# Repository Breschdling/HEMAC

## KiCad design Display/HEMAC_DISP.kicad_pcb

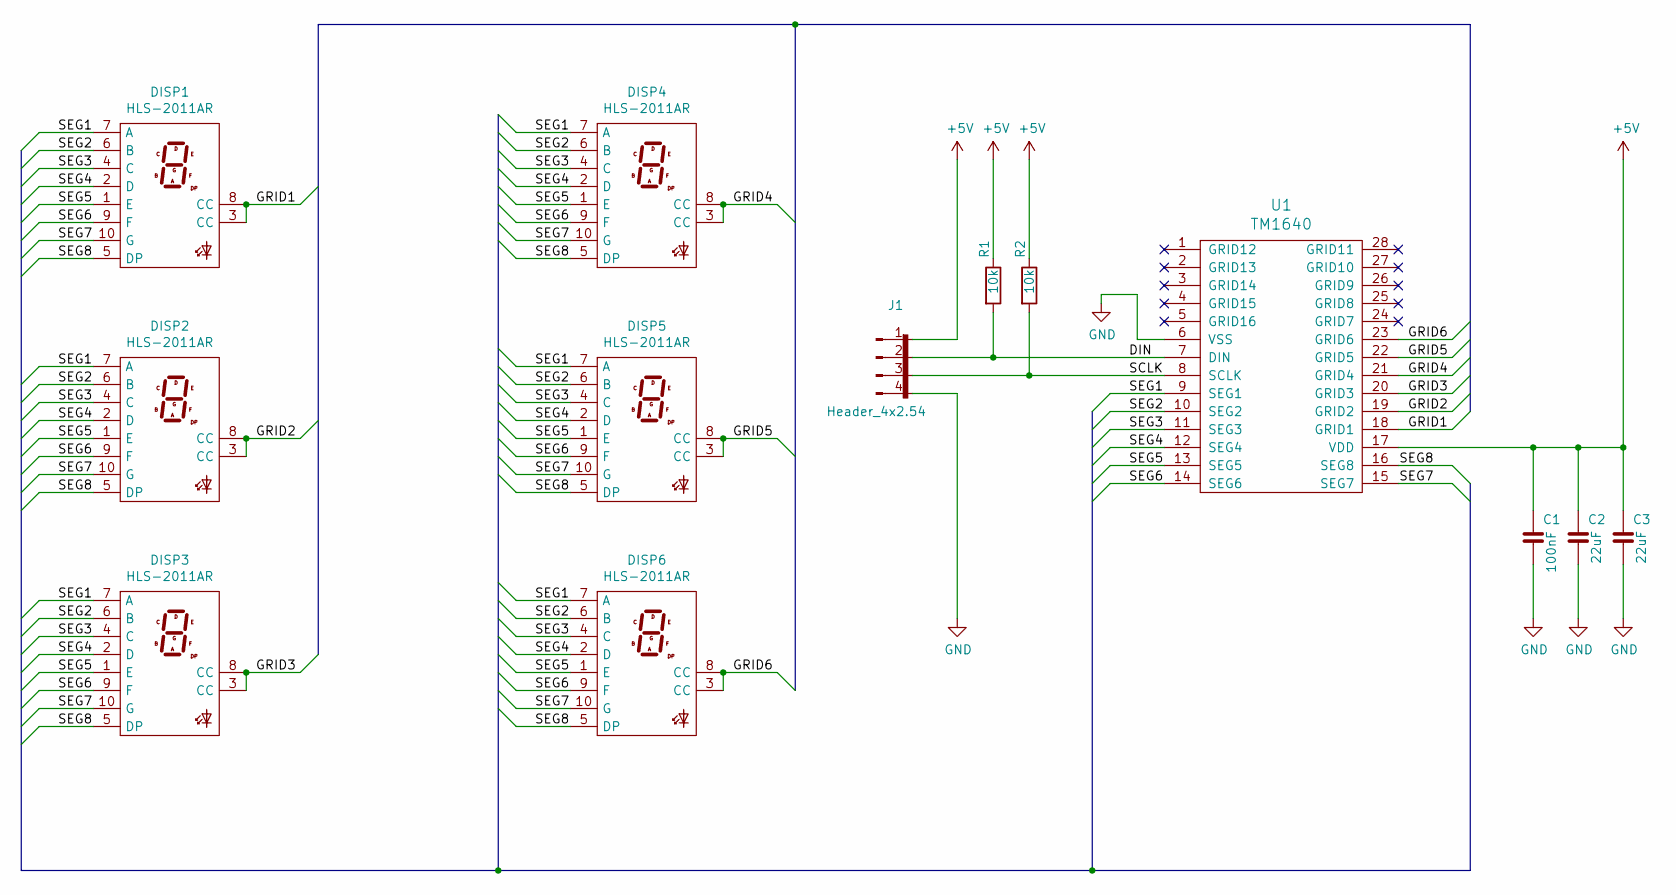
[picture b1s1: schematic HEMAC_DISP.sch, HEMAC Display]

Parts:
C1: 100nF; C_0805
C2, C3: 22uF; C_0805
DISP1, DISP2, DISP3, DISP4, DISP5, DISP6: HLS-2011AR; HLS-2011_Via
J1: Header_4x2.54; PinHeader_1x04_P2.54mm_Vertical
R1, R2: 10k; R_0805
U1: TM1640; SOIC28P127_1740X1015X255L60X40M

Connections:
+5V: C1.1, C2.1, C3.1, J1.1, R1.1, R2.1, U1.17 (VDD)
/DIN: J1.2, R1.2, U1.7 (DIN)
/GRID1: DISP1.3 (CC), DISP1.8 (CC), U1.18 (GRID1)
/GRID2: DISP2.3 (CC), DISP2.8 (CC), U1.19 (GRID2)
/GRID3: DISP3.3 (CC), DISP3.8 (CC), U1.20 (GRID3)
/GRID4: DISP4.3 (CC), DISP4.8 (CC), U1.21 (GRID4)
/GRID5: DISP5.3 (CC), DISP5.8 (CC), U1.22 (GRID5)
/GRID6: DISP6.3 (CC), DISP6.8 (CC), U1.23 (GRID6)
/SCLK: J1.3, R2.2, U1.8 (SCLK)
/SEG1: DISP1.7 (A), DISP2.7 (A), DISP3.7 (A), DISP4.7 (A), DISP5.7 (A), DISP6.7 (A), U1.9 (SEG1)
/SEG2: DISP1.6 (B), DISP2.6 (B), DISP3.6 (B), DISP4.6 (B), DISP5.6 (B), DISP6.6 (B), U1.10 (SEG2)
/SEG3: DISP1.4 (C), DISP2.4 (C), DISP3.4 (C), DISP4.4 (C), DISP5.4 (C), DISP6.4 (C), U1.11 (SEG3)
/SEG4: DISP1.2 (D), DISP2.2 (D), DISP3.2 (D), DISP4.2 (D), DISP5.2 (D), DISP6.2 (D), U1.12 (SEG4)
/SEG5: DISP1.1 (E), DISP2.1 (E), DISP3.1 (E), DISP4.1 (E), DISP5.1 (E), DISP6.1 (E), U1.13 (SEG5)
/SEG6: DISP1.9 (F), DISP2.9 (F), DISP3.9 (F), DISP4.9 (F), DISP5.9 (F), DISP6.9 (F), U1.14 (SEG6)
/SEG7: DISP1.10 (G), DISP2.10 (G), DISP3.10 (G), DISP4.10 (G), DISP5.10 (G), DISP6.10 (G), U1.15 (SEG7)
/SEG8: DISP1.5 (DP), DISP2.5 (DP), DISP3.5 (DP), DISP4.5 (DP), DISP5.5 (DP), DISP6.5 (DP), U1.16 (SEG8)
GND: C1.2, C2.2, C3.2, J1.4, U1.6 (VSS)

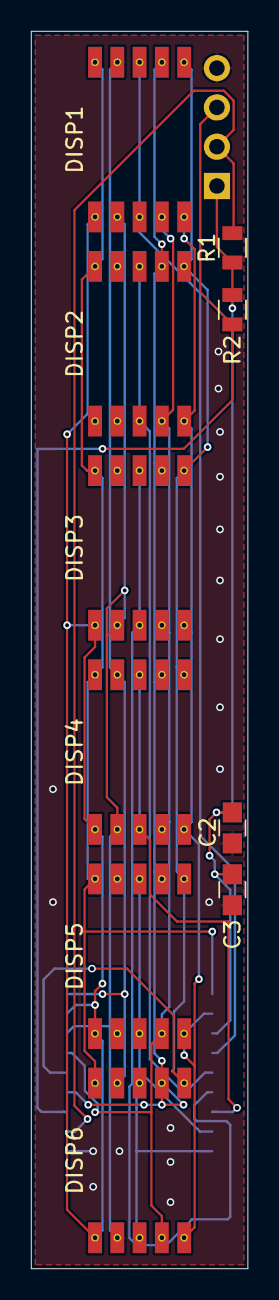
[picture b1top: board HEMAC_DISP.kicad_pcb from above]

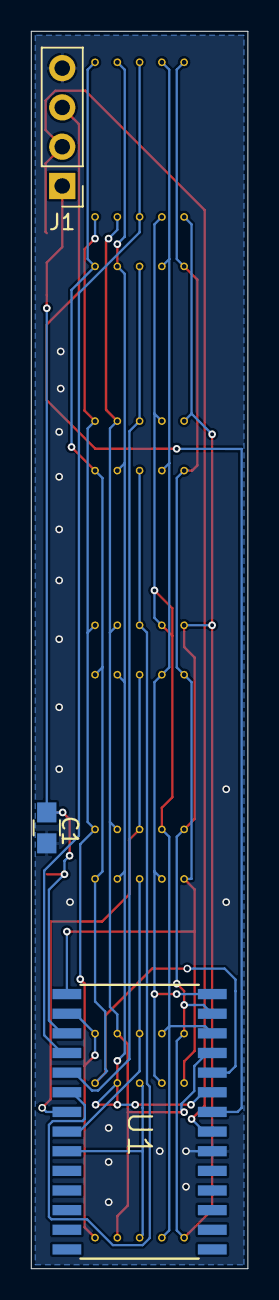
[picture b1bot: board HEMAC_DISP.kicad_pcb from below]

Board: 2 copper layers, 14.0 x 80.0 mm, 13 parts (3 on the bottom side), 18 nets.

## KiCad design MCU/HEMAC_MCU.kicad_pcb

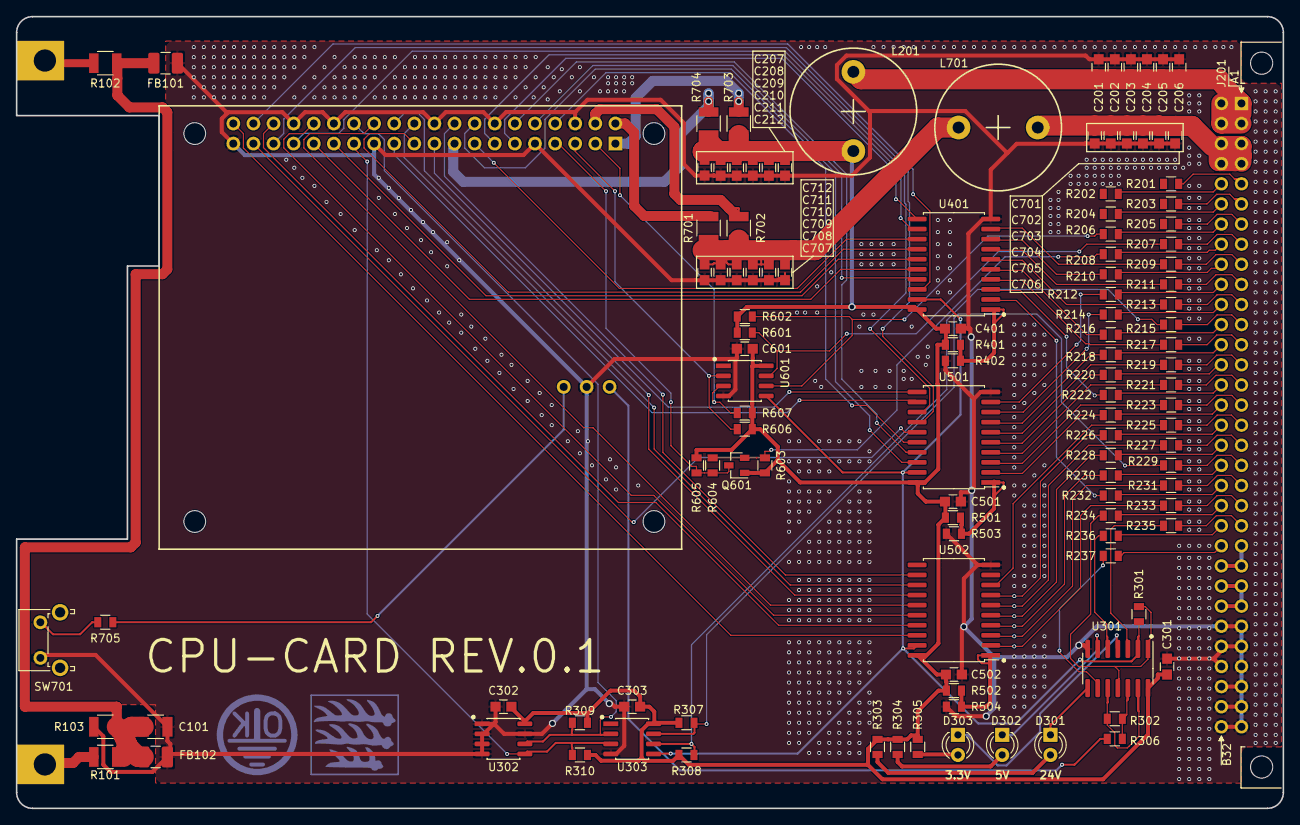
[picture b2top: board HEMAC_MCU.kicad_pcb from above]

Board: 2 copper layers, 160.0 x 100.0 mm, 119 parts (0 on the bottom side), 126 nets.

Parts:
C101: 1nF; C_1210
C201, C207, C301, C302, C303, C401, C501, C502, C601, C706, C712: 100nF; C_0805
C202, C203, C204, C205, C206, C208, C209, C210, C211, C212, C701, C702, C703, C704, C705, C707, C708, C709, C710, C711: 10uF; C_0805
D301, D302, D303: LED; LED_D3.0mm
FB101, FB102: 100R; FB_1210_3225Metric_Pad1.42x2.65mm_HandSolder
J201: DIN41612_2x32_B; DIN41612_B_2x32_Horizontal
L201, L701: 120uH_3A; 16mm_Radial
M101: Eurocard_Handle; EuroCard_Handle
Q601: 2N7002; SOT-23
R101, R102, R701, R702, R703, R704: 0R; R_1210
R103: 1M; R_1210
R201, R202, R203, R204, R205, R206, R207, R208, R209, R210, R211, R212, R213, R214, R215, R216, R217, R218, R219, R220, R221, R222, R223, R224, R225, R226, R227, R228, R229, R230, R231, R232, R233, R234, R235, R236, R237, R604, R705: 100R; R_0805
R301, R302, R306: 0R; R_0805
R303, R304, R305: 220R; R_0805
R307, R308, R309, R310: 3k9; R_0805
R401, R402, R501, R502, R503, R504: 1k; R_0805
R601, R602, R606, R607: 1k8; R_0805
R603, R605: 4k7; R_0805
SW701: Tactile_90_Degeree; SW_Tactile_SPST_Angled_PTS645Vx58-2LFS
U301: 74HC14D; SOIC-14_3.9x8.7mm_P1.27mm
U302: CAT24C32; SOIC-8_3.9x4.9mm_P1.27mm
U303, U601: PCA9515; SOIC-8_3.9x4.9mm_P1.27mm
U401, U501, U502: 74HC245; SOIC-20W_7.5x12.8mm_P1.27mm
X701: RPI_4+Run; raspberrypi4

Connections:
+3V3: C207.1, C208.1, C209.1, C210.1, C211.1, C212.1, C301.1, C302.1, C303.1, C401.1, C501.1, C502.1, C601.1, L201.2, Q601.1, R303.1, R304.1, R305.1, R307.1, R308.1, R309.1, R310.1, R401.2, R501.2, R502.2, R601.1, R602.1, R603.1, R605.1, R606.1, R607.1, R703.2, R704.2, U301.14, U302.8, U303.8, U401.20, U501.20, U502.20, U601.8
+5V: C701.1, C702.1, C703.1, C704.1, C705.1, C706.1, J201.A3, J201.A4, J201.B3, J201.B4, L701.2
+24V: J201.A23, J201.A24, J201.B24
/Bus/1_wire: Q601.2, R208.1, R603.2, R604.2
/Bus/#RESET: R234.1, R301.2, U301.1, U301.11
/Bus/CE0: R227.1, U502.6
/Bus/CE1: R228.1, U502.5
/Bus/CE2: R231.1, U502.3
/Bus/GPI5: R216.1, U401.5
/Bus/GPI6: R217.1, U401.4
/Bus/GPI17: R209.1, U401.9
/Bus/GPI22: R211.1, U401.7
/Bus/GPI27: R210.1, U401.8
/Bus/GPO23: R224.1, U501.2
/Bus/GPO24: R225.1, U502.8
/Bus/GPO25: R226.1, U502.7
/Bus/GPO26: R220.1, U501.5
/Bus/I2C_SCL: R207.1, R601.2, U601.7
/Bus/I2C_SDA: R206.1, R602.2, U601.6
/Bus/ID_SC: R229.1, R307.2, U303.7
/Bus/ID_SD: R215.1, R308.2, U303.6
/Bus/MISO: R213.1, U401.6
/Bus/MOSI: R212.1, U501.9
/Bus/PCM_CLK: R223.1, U501.3
/Bus/PCM_DIN: R232.1, U401.2
/Bus/PCM_DOUT: R233.1, U502.2
/Bus/PCM_FS: R219.1, U501.6
/Bus/PWM0: R230.1, U502.4
/Bus/PWM1: R218.1, U501.7
/Bus/PWR_3V3: R235.1, U301.3
/Bus/PWR_5V: R236.1, U301.5
/Bus/PWR_24V: R237.1, U301.9
/Bus/SCLK: R214.1, U501.8
/Bus/UART0_RXD: R222.1, U401.3
/Bus/UART0_TXD: R221.1, U501.4
/Computer/GPIO2: R607.2, U601.3, X701.3
/Computer/GPIO3: R606.2, U601.2, X701.5
/Computer/GPIO4: Q601.3, R604.1, R605.2, X701.7
/Computer/GPIO5: U401.15, X701.29
/Computer/GPIO6: U401.16, X701.31
/Computer/GPIO7: U502.15, X701.26
/Computer/GPIO8: U502.14, X701.24
/Computer/GPIO9: U401.14, X701.21
/Computer/GPIO10: U501.11, X701.19
/Computer/GPIO11: U501.12, X701.23
/Computer/GPIO12: U502.16, X701.32
/Computer/GPIO13: U501.13, X701.33
/Computer/GPIO14: U501.16, X701.8
/Computer/GPIO15: U401.17, X701.10
/Computer/GPIO16: U502.17, X701.36
/Computer/GPIO17: U401.11, X701.11
/Computer/GPIO18: U501.17, X701.12
/Computer/GPIO19: U501.14, X701.35
/Computer/GPIO20: U401.18, X701.38
/Computer/GPIO21: U502.18, X701.40
/Computer/GPIO22: U401.13, X701.15
/Computer/GPIO23: U501.18, X701.16
/Computer/GPIO24: U502.12, X701.18
/Computer/GPIO25: U502.13, X701.22
/Computer/GPIO26: U501.15, X701.37
/Computer/GPIO27: U401.12, X701.13
/Computer/ID_SC_RPI: R309.2, U302.6, U303.2, X701.28
/Computer/ID_SD_RPI: R310.2, U302.5, U303.3, X701.27
/Computer/RUN_PG2: R306.1, X701.43
/Inputs/CE: R301.1, U301.2, U303.5, U401.19, U501.19, U502.19, U601.5
Earth: C101.1, FB101.1, FB102.1, R101.1, R102.1, R103.1
GND: C101.2, C201.2, C202.2, C203.2, C204.2, C205.2, C206.2, C207.2, C208.2, C209.2, C210.2, C211.2, C212.2, C301.2, C302.2, C303.2, C401.2, C501.2, C502.2, C601.2, C701.2, C702.2, C703.2, C704.2, C705.2, C706.2, C707.2, C708.2, C709.2, C710.2, C711.2, C712.2, FB101.2, FB102.2, J201.A27, J201.A28, J201.A29, J201.A30, J201.A31, J201.A32, J201.B27, J201.B28, J201.B29, J201.B30, J201.B31, J201.B32, R103.2, R402.1, R503.1, R504.1, SW701.1, U301.7, U302.1, U302.2, U302.3, U302.4, U302.7, U303.4, U401.10, U501.10, U502.10, U601.4, X701.6, X701.9, X701.14, X701.20, X701.25, X701.30, X701.34, X701.39, X701.42
unnamed: C201.1, C202.1, C203.1, C204.1, C205.1, C206.1, J201.A1, J201.A2, J201.B1, J201.B2, L201.1
unnamed: C707.1, C708.1, C709.1, C710.1, C711.1, C712.1, L701.1, R701.2, R702.2
unnamed: D301.1, U301.8
unnamed: D301.2, R303.2
unnamed: D302.1, U301.6
unnamed: D302.2, R304.2
unnamed: D303.1, U301.4
unnamed: D303.2, R305.2
unnamed: J201.A5, R201.2
unnamed: J201.A6, R203.2
unnamed: J201.A7, R205.2
unnamed: J201.A8, R207.2
unnamed: J201.A9, R209.2
unnamed: J201.A10, R211.2
unnamed: J201.A11, R213.2
unnamed: J201.A12, R215.2
unnamed: J201.A13, R217.2
unnamed: J201.A14, R219.2
unnamed: J201.A15, R221.2
unnamed: J201.A16, R223.2
unnamed: J201.A17, R225.2
unnamed: J201.A18, R227.2
unnamed: J201.A19, R229.2
unnamed: J201.A20, R231.2
unnamed: J201.A21, R233.2
unnamed: J201.A22, R235.2
unnamed: J201.B5, R202.2
unnamed: J201.B6, R204.2
unnamed: J201.B7, R206.2
unnamed: J201.B8, R208.2
unnamed: J201.B9, R210.2
unnamed: J201.B10, R212.2
unnamed: J201.B11, R214.2
unnamed: J201.B12, R216.2
unnamed: J201.B13, R218.2
unnamed: J201.B14, R220.2
unnamed: J201.B15, R222.2
unnamed: J201.B16, R224.2
unnamed: J201.B17, R226.2
unnamed: J201.B18, R228.2
unnamed: J201.B19, R230.2
unnamed: J201.B20, R232.2
unnamed: J201.B21, R234.2
unnamed: J201.B22, R236.2
unnamed: J201.B23, R237.2
unnamed: M101.1, R101.2
unnamed: M101.2, R102.2
unnamed: R302.1, R306.2, U301.12
unnamed: R302.2, U301.10, U301.13
unnamed: R401.1, R402.2, U401.1
unnamed: R501.1, R503.2, U501.1
unnamed: R502.1, R504.2, U502.1
unnamed: R701.1, X701.2
unnamed: R702.1, X701.4
unnamed: R703.1, X701.1
unnamed: R704.1, X701.17
unnamed: R705.1, X701.41
unnamed: R705.2, SW701.2
VDC: J201.A25, J201.A26, J201.B25, J201.B26

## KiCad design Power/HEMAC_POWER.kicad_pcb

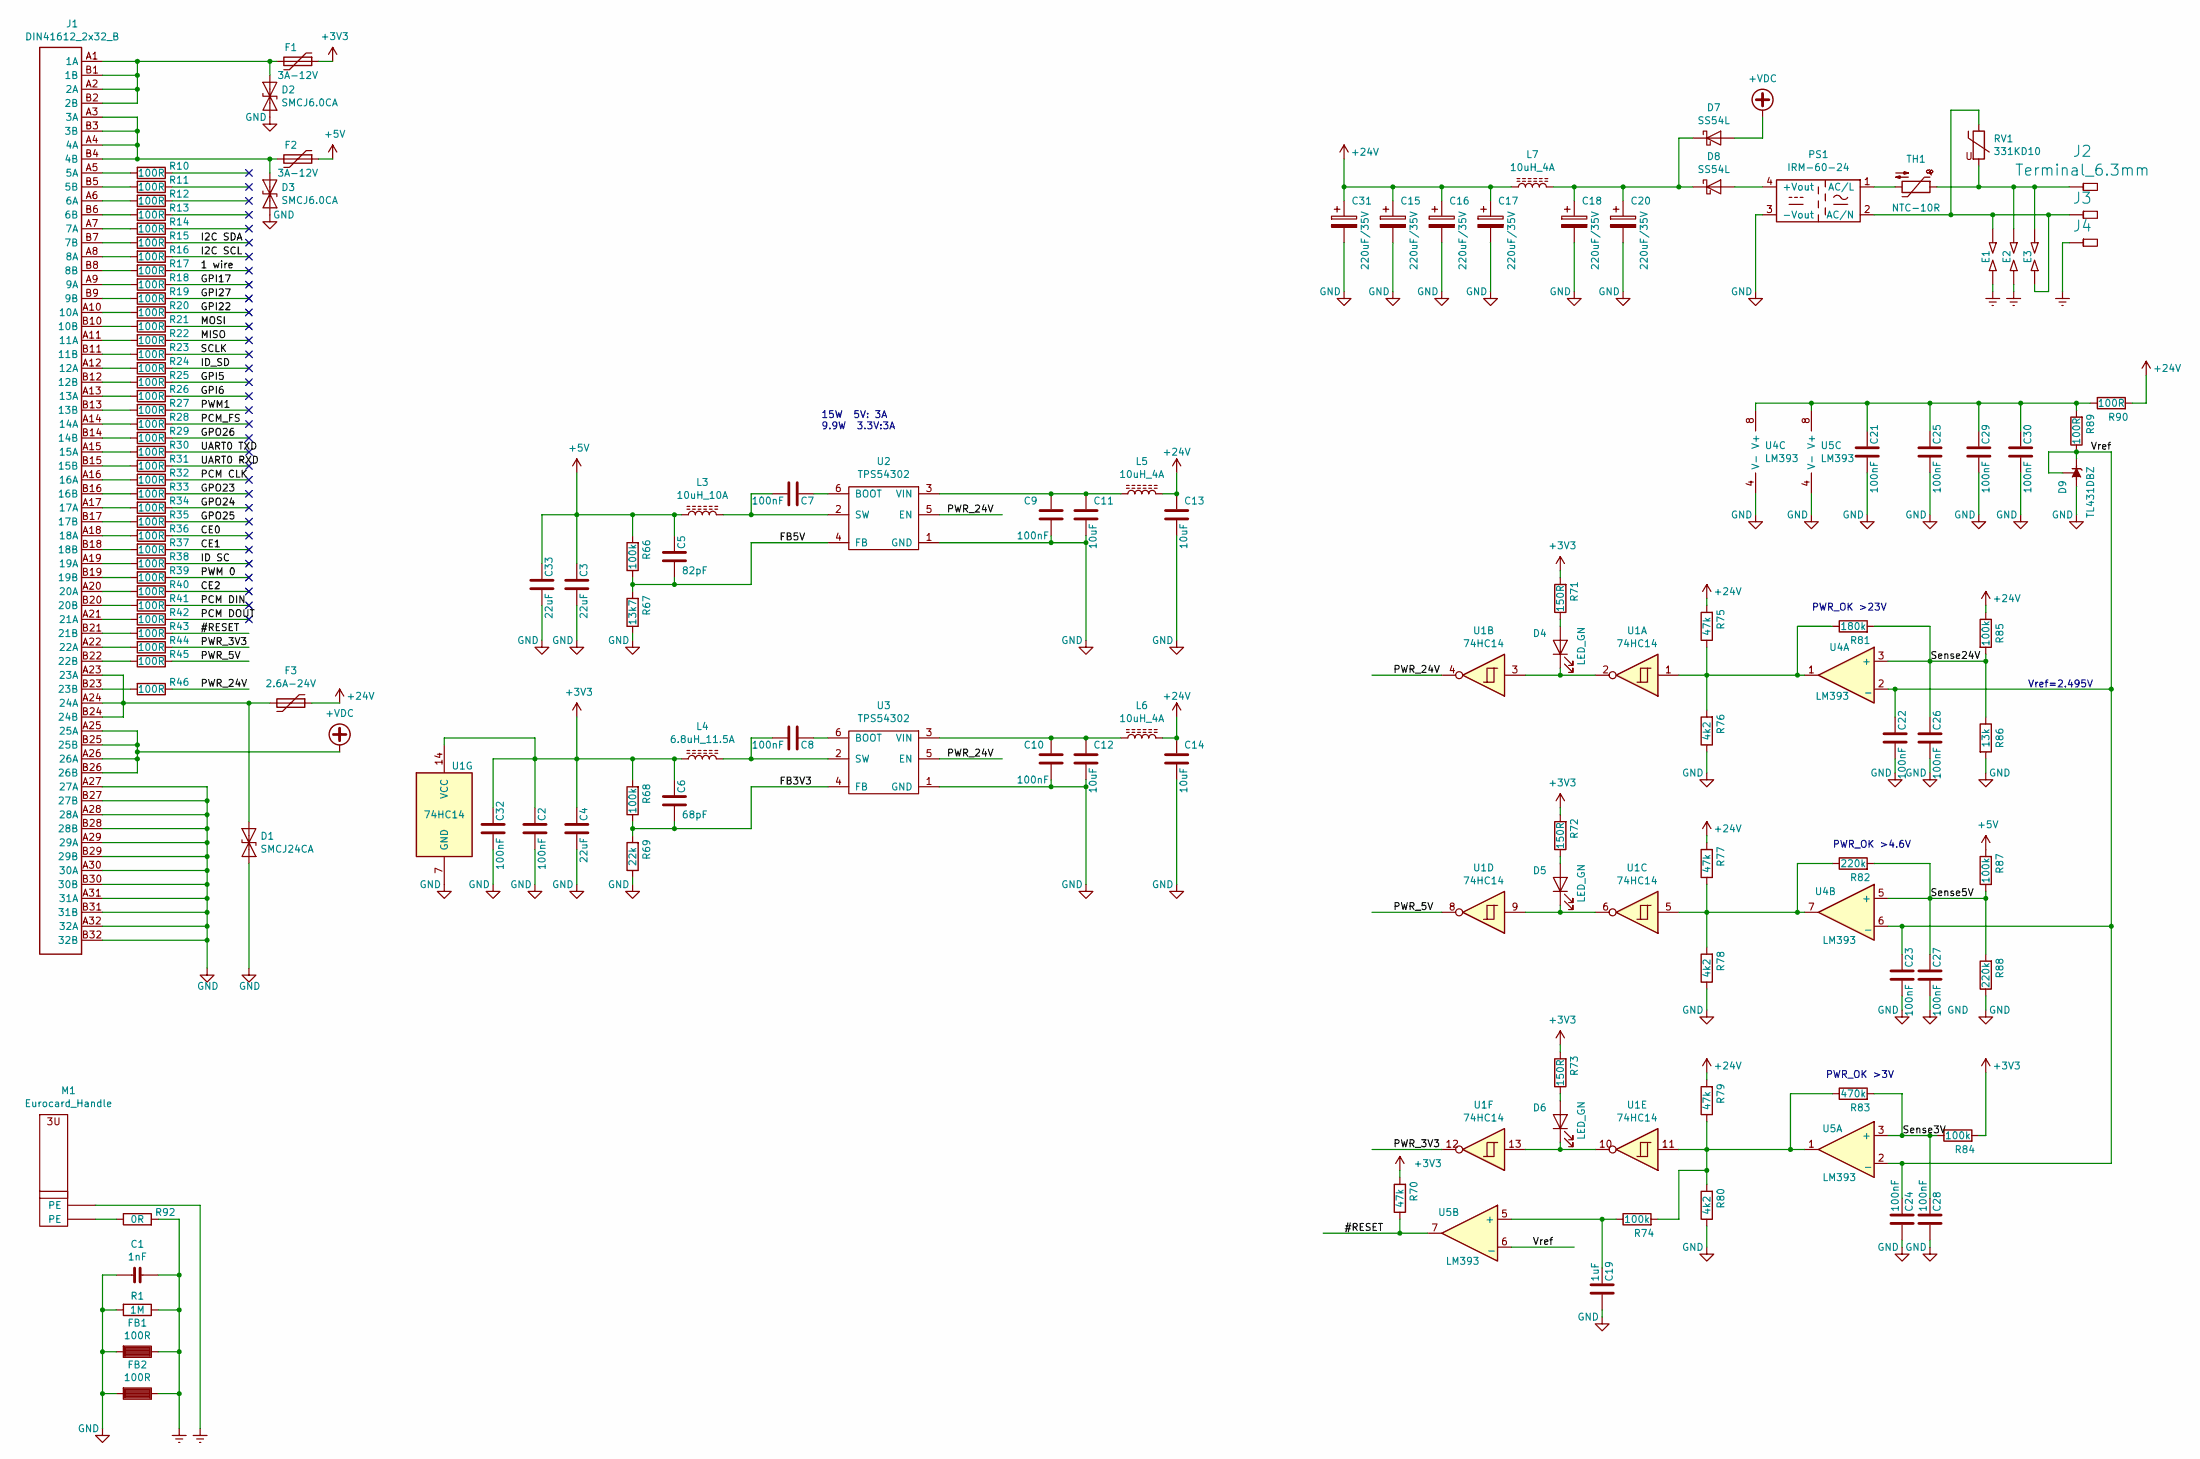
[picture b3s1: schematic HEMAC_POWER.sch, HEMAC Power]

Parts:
C1: 1nF; C_1210_3225Metric_Pad1.42x2.65mm_HandSolder
C2, C7, C8, C9, C10, C21, C22, C23, C24, C25, C26, C27, C28, C29, C30: 100nF; C_0805_HandSoldering
C3, C4: 22uF; C_0805_HandSoldering
C5: 82pF; C_0805_HandSoldering
C6: 68pF; C_0805_HandSoldering
C11, C12, C13, C14: 10uF; C_0805_HandSoldering
C15, C16, C17, C18, C20, C31: 220uF/35V; CP_Radial_D8.0mm_P3.50mm
C19: 1uF; C_0805_HandSoldering
C32: 100nF; C_0805_2012Metric_Pad1.15x1.40mm_HandSolder
C33: 22uF; C_0805_2012Metric_Pad1.15x1.40mm_HandSolder
D1: SMCJ24CA; D_SMC
D2, D3: SMCJ6.0CA; D_SMC
D4, D5, D6: LED_GN; LED_D3.0mm
D7, D8: SS54L; D_SMC_Handsoldering
D9: TL431DBZ; SOT-23
E1, E2, E3: SPARK_GAP_0.5mm; SparkGap_0.5
F1, F2: 3A-12V; Fuse_SMD2920
F3: 2.6A-24V; Fuse_SMD2920
FB1, FB2: 100R; FB_1210_3225Metric_Pad1.42x2.65mm_HandSolder
J1: DIN41612_2x32_B; DIN41612_B_2x32_Horizontal
J2, J3, J4: Terminal_6.3mm; Terminal_6.3mm_THT
L3: 10uH_10A; Inductor_13.5x12.5
L4: 6.8uH_11.5A; Inductor_13.5x12.5
L5, L6, L7: 10uH_4A; Inductor_7.1x6.6
M1: Eurocard_Handle; EuroCard_Handle
PS1: IRM-60-24; IRM-60
R1: 1M; R_1210_3225Metric_Pad1.42x2.65mm_HandSolder
R10, R11, R12, R13, R14, R15, R16, R17, R18, R19, R20, R21, R22, R23, R24, R25, R26, R27, R28, R29, R30, R31, R32, R33, R34, R35, R36, R37, R38, R39, R40, R41, R42, R43, R44, R45, R46, R89, R90: 100R; R_0805_HandSoldering
R66, R68, R74, R84, R85, R87: 100k; R_0805_HandSoldering
R67: 13k7; R_0805_HandSoldering
R69: 22k; R_0805_HandSoldering
R70, R75, R77, R79: 47k; R_0805_HandSoldering
R71, R72, R73: 150R; R_0805_HandSoldering
R76, R78, R80: 4k2; R_0805_HandSoldering
R81: 180k; R_0805_HandSoldering
R82, R88: 220k; R_0805_HandSoldering
R83: 470k; R_0805_HandSoldering
R86: 13k; R_0805_HandSoldering
R92: 0R; R_1812_HandSoldering
RV1: 331KD10; D12mm_W5.4mm_P7.5mm
TH1: NTC-10R; RV_Disc_D12_W3.9_P7.5
U1: 74HC14; SOIC-14_3.9x8.7mm_Pitch1.27mm
U2, U3: TPS54302; SOT-23-6_Handsoldering
U4, U5: LM393; SOIC-8_3.9x4.9mm_Pitch1.27mm

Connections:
+3V3: C2.1, C4.1, C6.1, C32.1, F1.1, L4.1, R68.2, R70.2, R71.2, R72.2, R73.2, R84.2, U1.14 (VCC)
+5V: C3.1, C5.1, C33.1, F2.1, L3.1, R66.2, R87.2
+24V: C13.1, C14.1, C15.1, C16.1, C17.1, C31.1, F3.1, L5.2, L6.2, L7.1, R75.2, R77.2, R79.2, R85.1, R90.2
/1 wire: R17.1
/#RESET: R43.1, R70.1, U5.7
/CE0: R36.1
/CE1: R37.1
/CE2: R40.1
/FB3V3: C6.2, R68.1, R69.2, U3.4 (FB)
/FB5V: C5.2, R66.1, R67.2, U2.4 (FB)
/GPI5: R25.1
/GPI6: R26.1
/GPI17: R18.1
/GPI22: R20.1
/GPI27: R19.1
/GPO23: R33.1
/GPO24: R34.1
/GPO25: R35.1
/GPO26: R29.1
/I2C SCL: R16.1
/I2C SDA: R15.1
/ID SC: R38.1
/ID_SD: R24.1
/MISO: R22.1
/MOSI: R21.1
/PCM CLK: R32.1
/PCM DIN: R41.1
/PCM DOUT: R42.1
/PCM_FS: R28.1
/PWM1: R27.1
/PWM 0: R39.1
/PWR_3V3: R44.1, U1.12
/PWR_5V: R45.1, U1.8
/PWR_24V: R46.1, U1.4, U2.5 (EN), U3.5 (EN)
/SCLK: R23.1
/Sense3V: C28.1, R83.2, R84.1, U5.3 (+)
/Sense5V: C27.1, R82.2, R87.1, R88.2, U4.5 (+)
/Sense24V: C26.1, R81.2, R85.2, R86.1, U4.3 (+)
/UART0 RXD: R31.1
/UART0 TXD: R30.1
/Vref: C22.1, C23.1, C24.1, D9.1 (K), D9.2 (REF), R89.1, U4.2 (_), U4.6 (_), U5.2 (_), U5.6 (_)
Earth: C1.1, E1.2, E2.2, FB1.1, FB2.1, J4.1, M1.1, R1.1, R92.2
GND: C1.2, C2.2, C3.2, C4.2, C9.2, C10.2, C11.2, C12.2, C13.2, C14.2, C15.2, C16.2, C17.2, C18.2, C19.2, C20.2, C21.2, C22.2, C23.2, C24.2, C25.2, C26.2, C27.2, C28.2, C29.2, C30.2, C31.2, C32.2, C33.2, D1.2 (A2), D2.2 (A2), D3.2 (A2), D9.3 (A), FB1.2, FB2.2, J1.A27 (27A), J1.A28 (28A), J1.A29 (29A), J1.A30 (30A), J1.A31 (31A), J1.A32 (32A), J1.B27 (27B), J1.B28 (28B), J1.B29 (29B), J1.B30 (30B), J1.B31 (31B), J1.B32 (32B), PS1.3 (-Vout), R1.2, R67.1, R69.1, R76.1, R78.1, R80.1, R86.2, R88.1, U1.7 (GND), U2.1 (GND), U3.1 (GND), U4.4 (V-), U5.4 (V-)
unnamed: C7.1, U2.6 (BOOT)
unnamed: C7.2, L3.2, U2.2 (SW)
unnamed: C8.1, U3.6 (BOOT)
unnamed: C8.2, L4.2, U3.2 (SW)
unnamed: C10.1, C12.1, L6.1, U3.3 (VIN)
unnamed: C9.1, C11.1, L5.1, U2.3 (VIN)
unnamed: C18.1, C20.1, D7.1 (K), D8.1 (K), L7.2
unnamed: C19.1, R74.1, U5.5 (+)
unnamed: C21.1, C25.1, C29.1, C30.1, R89.2, R90.1, U4.8 (V+), U5.8 (V+)
unnamed: D1.1 (A1), F3.2, J1.A23 (23A), J1.A24 (24A), J1.B24 (24B)
unnamed: D2.1 (A1), F1.2, J1.A1 (1A), J1.A2 (2A), J1.B1 (1B), J1.B2 (2B)
unnamed: D3.1 (A1), F2.2, J1.A3 (3A), J1.A4 (4A), J1.B3 (3B), J1.B4 (4B)
unnamed: D4.1 (K), U1.2, U1.3
unnamed: D4.2 (A), R71.1
unnamed: D5.1 (K), U1.6, U1.9
unnamed: D5.2 (A), R72.1
unnamed: D6.1 (K), U1.10, U1.13
unnamed: D6.2 (A), R73.1
unnamed: D8.2 (A), PS1.4 (+Vout)
unnamed: E1.1, E3.2, J3.1, PS1.2 (AC/N), RV1.1
unnamed: E2.1, E3.1, J2.1, RV1.2, TH1.1
unnamed: J1.A5 (5A), R10.2
unnamed: J1.A6 (6A), R12.2
unnamed: J1.A7 (7A), R14.2
unnamed: J1.A8 (8A), R16.2
unnamed: J1.A9 (9A), R18.2
unnamed: J1.A10 (10A), R20.2
unnamed: J1.A11 (11A), R22.2
unnamed: J1.A12 (12A), R24.2
unnamed: J1.A13 (13A), R26.2
unnamed: J1.A14 (14A), R28.2
unnamed: J1.A15 (15A), R30.2
unnamed: J1.A16 (16A), R32.2
unnamed: J1.A17 (17A), R34.2
unnamed: J1.A18 (18A), R36.2
unnamed: J1.A19 (19A), R38.2
unnamed: J1.A20 (20A), R40.2
unnamed: J1.A21 (21A), R42.2
unnamed: J1.A22 (22A), R44.2
unnamed: J1.B5 (5B), R11.2
unnamed: J1.B6 (6B), R13.2
unnamed: J1.B7 (7B), R15.2
unnamed: J1.B8 (8B), R17.2
unnamed: J1.B9 (9B), R19.2
unnamed: J1.B10 (10B), R21.2
unnamed: J1.B11 (11B), R23.2
unnamed: J1.B12 (12B), R25.2
unnamed: J1.B13 (13B), R27.2
unnamed: J1.B14 (14B), R29.2
unnamed: J1.B15 (15B), R31.2
unnamed: J1.B16 (16B), R33.2
unnamed: J1.B17 (17B), R35.2
unnamed: J1.B18 (18B), R37.2
unnamed: J1.B19 (19B), R39.2
unnamed: J1.B20 (20B), R41.2
unnamed: J1.B21 (21B), R43.2
unnamed: J1.B22 (22B), R45.2
unnamed: J1.B23 (23B), R46.2
unnamed: M1.2, R92.1
unnamed: PS1.1 (AC/L), TH1.2
unnamed: R74.2, R79.1, R80.2, R83.1, U1.11, U5.1
unnamed: R75.1, R76.2, R81.1, U1.1, U4.1
unnamed: R77.1, R78.2, R82.1, U1.5, U4.7
VDC: D7.2 (A), J1.A25 (25A), J1.A26 (26A), J1.B25 (25B), J1.B26 (26B)

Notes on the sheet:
PWR_OK >23V
15W 5V: 3A 9.9W 3.3V:3A
PWR_OK >4.6V
PWR_OK >3V
Vref=2.495V

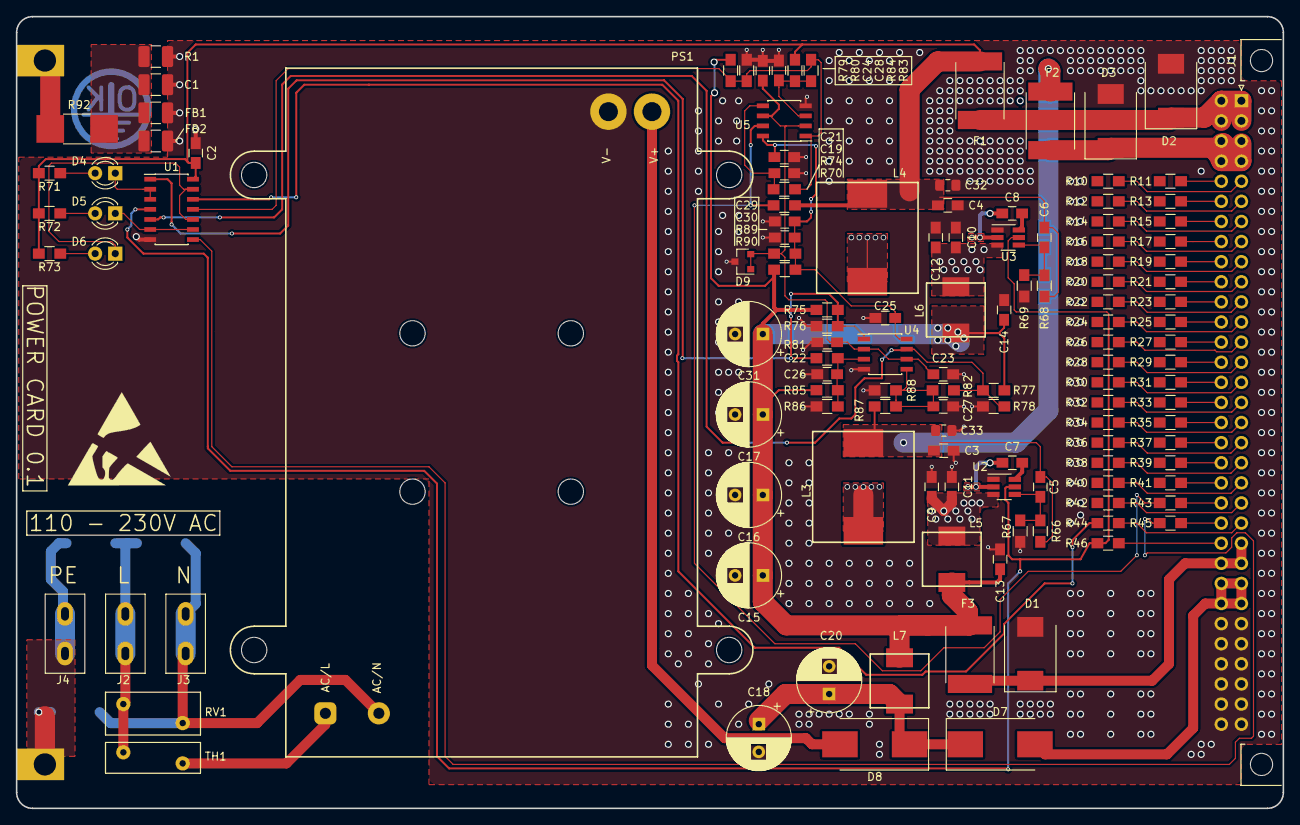
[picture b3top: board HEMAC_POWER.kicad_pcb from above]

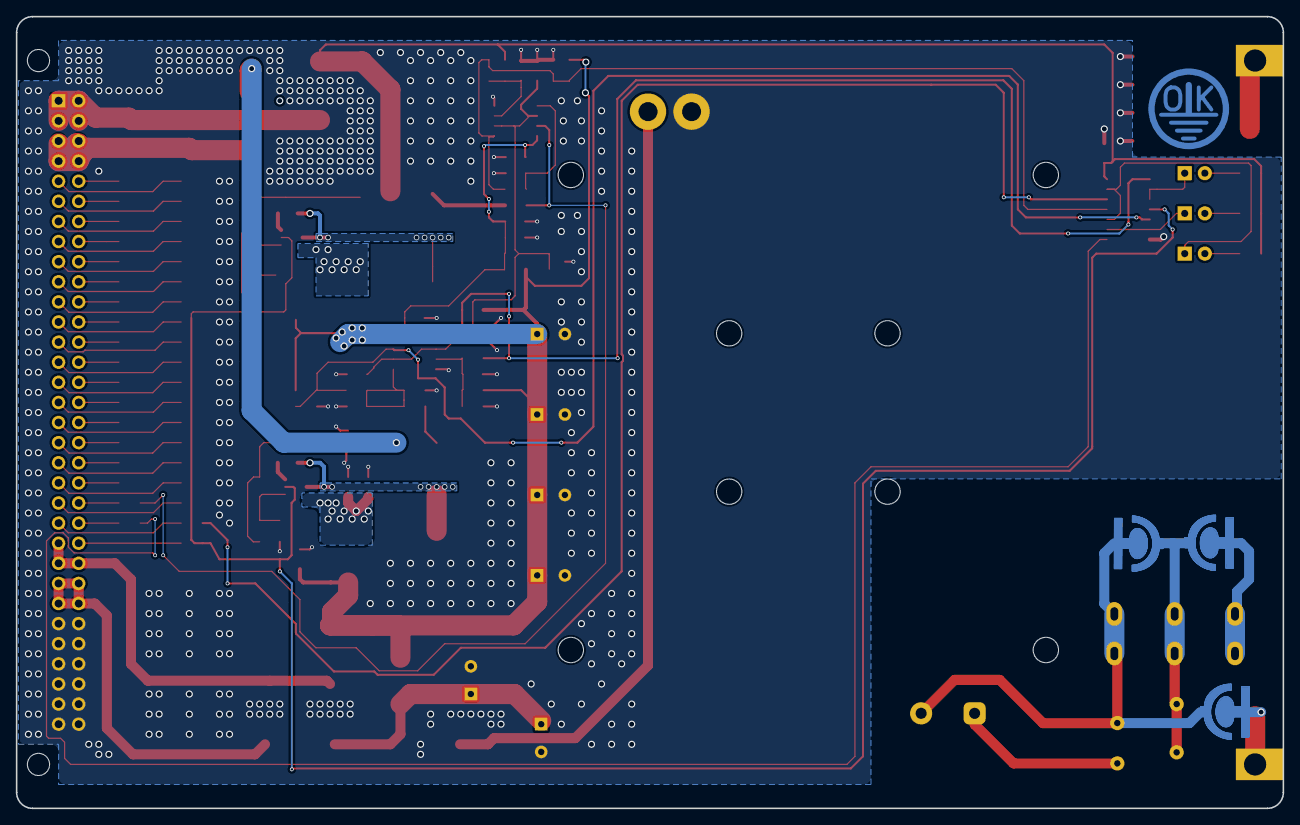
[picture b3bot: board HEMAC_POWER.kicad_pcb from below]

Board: 2 copper layers, 160.0 x 100.0 mm, 132 parts (3 on the bottom side), 79 nets.
